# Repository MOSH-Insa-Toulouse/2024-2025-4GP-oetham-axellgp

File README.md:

# 2024-2025-4GP-oetham-axellgp

## Contexte

Projet réalisé dans le cadre du cours "du capteur au banc de test", lors du deuxième semestre de l'année 2024-2025 de la formation 4ème année Génie Physique. Notre point de référence est l'article _"Pencil Drawn Strain Gauges and Chemiresistors on Paper"_ (Cheng-Wei Lin, Zhibo Zhao, Jaemyung Kim & Jiaxing Huang). Notre capteur est composé d'un simple bout de papier avec du graphite déposé dessus par un crayon à papier. Avec une simple déformation du papier, nous pouvons mesurer la déformation des particules. Le système granulaire du papier subit une modification de résistance et de conductance. Ainsi, nous pourrons utiliser ce capteur comme une jauge de contrainte traditionnelle.

L'objectif de ce projet est de pouvoir réaliser, étape par étape, un dispositif qui nous permettra de mesurer une déformation d'un capteur low-tech.

## Sommaire

- [Contexte](#contexte)
- [Sommaire](#sommaire)
- [Livrables](#livrables)
- [Matériel nécessaire](#matériel-nécessaire)
- [Simulation sur LTSpice](#simulation-sur-ltspice)
- [Design du PCB](#design-du-pcb)
- [Réalisation du Shield](#réalisation-du-shield)
- [Code Arduino](#code-arduino)
- [Application MIT](#application-mit)
- [Datasheet](#datasheet)
- [Conclusion](#conclusion)
- [Contact](#contact)

## Livrables

- Un shield PCB permettant à se relier à une carte Arduino UNO. Ce shield aura à disposition plusieurs composants : un capteur de graphite, un module bluetooth, un ecran OLED, un encodeur rotatoire et un amplificateur transimpédance avec un potentiometre digital.
- Un code Arduino qui pilotera les différents composants.
- Une application Android réalisée sous MIT App Inventor.
- Une datasheet du capteur de graphite avec les données venant d'un banc de test mis en place par les étudiants.

## Matériel nécessaire

Pour produire notre shield, nous avons besoin du matériel suivant :

- Des résistances
- Des capacités
- Un Arduino UNO
- Un amplificateur opérationnel (LTC1050)
- Un potentiomètre digital (MCP41050)
- Un écran OLED
- Un encodeur rotatoire
- Un module bluetooth (HC-05)
- Un servo moteur
- Un flex sensor

## Simulation sur LTSpice

La résistance interne de notre capteur de graphite est de l'ordre du $\text{G}\Omega$. Le courant généré lorsque nous appliquons une tension de 5V est très faible. Pour pouvoir utiliser ce signal, nous le faisons passer par un amplificateur transimpédance. Ce montage est constitué d'un amplificateur opérationnel (AO) pour fournir un signal suffisamment large au convertisseur analogique-numérique (ADC) de l'Arduino UNO.

Nous avons choisi un AO de type LTC1050, car il possède une capacité à accepter en entrée un courant très faible et un offset de tension bas. Nous avons besoin d'un offset faible pour ne pas fausser les valeurs de tension envoyées à l'ADC que nous aurons besoin pour la suite.

Dans notre amplificateur, nous avons trois types de filtres différents :

- À l'entrée, un filtre passe-bas passif (composants : $R_1, C_1$) avec une fréquence de coupure de 16Hz. Cela permet de filtrer les bruits du courant en entrée.
- Un autre filtre passe-bas actif de fréquence de coupure de 1.6Hz (composants : $R_3, C_4$) couplé à l'AO. Ce filtre permet d'enlever la composante du bruit à 50Hz du réseau.
- En sortie, un dernier filtre (composants : $R_6, C_2$) de 1.6kHz qui permet de retirer le bruit créé pendant le traitement i.e. bruits des alimentations, de l'horloge...

La résistance $R_5$ est placé en amont de l'AO pour le protéger contre des décharges électrostatiques. Pour notre simulation, nous avons placé la capacité $C_3$ de sorte à ce qu'elle filtre le bruit de l'alimentation. Ainsi, la résistance $R_2$ sera remplacé par une résistance variable (un potentiomètre digital) qui va nous permettre de régler le gain de notre AO en fonction de notre besoin.

Une photo pour montrer que notre montage permet à amplifier notre signal du capteur :

Le signal de sortie est amplifié à 1V, ce qui sera assez pour que notre Arduino puisse le mesurer.

Ensuite, la réponse lorsque nous simulons un courant alternatif pour vérifier que le bruit est bien filtré :

Le bruit du réseau est atténué d'environ 72dB.

La simulation se trouve dans [ce dossier](/LTSpice/).

## Design du PCB

Pour réaliser notre printed circuit board (PCB), nous avons utilisé le logiciel KiCAD 9.0. Dans le logiciel, nous disposons de plusieurs outils de design comme la vue schématique des composants et la vue design du PCB.

La résistance $\text{R}_2$ a été remplace par un potentiomètre numérique de manière à faire varier le gain de notre amplificateur opérationnel (LTC1050). Nous avons également rajouté des composants en plus pour mesurer plus précisément notre capteur graphite. Ces composants seront déposés sur un shield d'Arduino UNO construit à partir d'un Gerber KiCAD.

- Un flex sensor
- Un écran OLED
- Un servo moteur
- Un module bluetooth HC-05

Ensuite, nous avons commencé par réaliser les symboles des composants avec leur schéma électrique sur la partie schématique de KiCAD. Le schéma électrique de l'ensemble de notre shield :

Par la suite, nous avons créé les empreintes de nos composants puis placées sur notre PCB sur la face PCB de KiCAD. Notre objectif pendant le routage était d'éviter les vias entraînées par le placement des composants. Le PCB créé sur le logiciel :

La beauté du logiciel est due au fait que nous pouvons générer une vue 3D du shield afin de pouvoir visualiser et vérifier l'emplacement de nos composants. La vue 3D sur KiCAD :

Vous pouvez retrouver toutes les ressources de KiCAD dans notre [dossier KiCAD](/KiCAD/projet-capteur/).

## Réalisation du Shield

Avec l'aide de Catherine Crouzet (aka Cathy pour les 4GP), nous avons fabriqué notre propre PCB. Après avoir envoyé notre fichier Gerber, qui sert comme masque de gravure, Cathy a placé ce masque sur une couche fine de cuivre sur une plaquette d'epoxy. Ensuite, il faut isoler la plaquette, puis l'expose aux UV. Une fois terminer, elle plonge la plaquette dans un bain révélateur afin de retirer la résine non-isolée. Finalement, elle nettoie la plaquette avec de l'acétone pour enlever la résine restante.

Nous avons ensuite effectué au perçage de notre plaquette grâce à une perceuse. On pourra ensuite poser et souder nos composants sur le PCB.

Voici une photo du PCB sur l'Arduino UNO avec tout les composants poser dessus :

## Code Arduino

Le code Arduino a été développé sur l'IDE Arduino 2.3.5. Nous avons utilisé les librairies Adafruit_SSD1306 pour piloter l'écran OLED et SoftwareSerial pour le HC-05. L'écran OLED utilise beaucoup de RAM. Pour contourner ce problème, nous avons utilisé la fonction ```F("Enter String")``` qui envoie les données sur la mémoire flash.

Au lancement du programme, qui est situé [ici](/Arduino/Test-Sensor/), une première calibration est faite à 3V sur le potentiomètre digital pour ne pas saturer la sortie sur l'ADC de l'Arduino. Cette calibration peut être refaite avec un simple appel sur l'application. Nous avons composé un menu avec trois choix :

- Menu 1 : Graphite Sensor
- Menu 2 : Flex Sensor
- Menu 3 : Servo Motor

Le choix du menu se fait avec l'encodeur rotatoire en le tournant pour sélectionner son menu désiré puis ensuite appuyer dessus pour valider la sélection.

Chaque choix du menu appelle une fonction différente qui réalise sa mesure. L'acquisition des données se fait toutes les 200ms. Pour chaque donnée, il faut convertir ce qu'on reçoit par la résolution de l'Arduino qui est de 1024 bytes. Le calcul de la résistance du capteur graphite se fait avec la formule suivante : $R_{es} = R_2 * (1 + \frac{R_4}{R_3}) * \frac{V_{CC}}{V_{graph}} - R_2 - R_1$. L'appellation des résistances est en accord avec notre schématique KiCAD.

## Application MIT

L'application Android a été développé sous MIT App Inventor. Elle reçoit les donnes de notre Capteur Graphite et de Flexion et nous pouvons aussi lui envoyer une position pour le Servo Moteur.

La face-avant de l'application nous donne la possibilité de rentrée dans plusieurs menus :

- Capteur Graphite
- Capteur Flexion
- Servo Moteur

Une fonctionnalité du menu Capteur Graphite est que nous pouvions calibrer directement le capteur depuis l'application s'il y a eu des changements de configuration.

Le menu Capteur Flexion propose un graphique où nous voyons la variation de la résistance du capteur.

Le menu Servo Moteur propose une roue tactile que nous pouvons régler afin d'envoyer la position désirer du Servo Moteur.

Vous pouvez vous rendre dans [ce dossier](/Android/) pour installer l'application MIT App Inventor ainsi voir les blocks de code qui contrôlent l'application.

## Datasheet

Pour effectuer des mesures, nous avons utilisé une impression 3D de demi-cercles avec des rayons différents.

Les diamètres des demi-cercles vont de 2cm jusqu'à 5cm avec un pas de 0.5cm. Avec la déformation $\epsilon = \frac{e}{D}$ et la résistance électrique $\frac{\Delta R}{R_0}$, nous pouvons tracer les courbes caractéristiques pour des crayons de type F, HB, 4B, 5B :

D'autant plus, nous n'avons aucun moyen pour bien s'assurer que la quantité déposée sur le capteur est la même. Ainsi, à chaque mesure, il y a un nouveau paramètre qui n'est pas le même i.e. on n'écrit pas de la même manière, on applique une force différente pour écrire, on n'applique pas le même angle de déformation. Ces derniers induisent une grosse variation dans la résistance mesurée.

Il se trouve que le flex sensor commercial est bien plus sensible à la déformation d'autant plus il peut être réutiliser beaucoup plus de fois que notre capteur en papier. Notre capteur a chaque utilisation perd de la précision qui impacte notre mesure de résistance. Par contre, notre capteur peut mesurer des résistances dans les $M\Omega$ comparer au flex sensor qui lui peut seulement mesurer des $k\Omega$.

La datasheet se trouve [ici](/Datasheet/).

## Conclusion

Notre capteur a un super potentiel en tant que capteur industriel. Il faudrait à tout prix trouver une méthode pour homogénéiser le dépôt du graphite. Le capteur est peu cher et sensible à des variations en tension ou compression. Nous conseillons de trouver une méthode pour bien appliquer la même force, le même dépôt de graphite et aussi trouver un papier plus adapté à la déformation. Ceci permettra de réaliser un capteur plus performant avec un potentiel plus élevé pour être industrialisable.

Pour le moment, notre capteur en papier est un super outil pour pouvoir comprendre et conceptionner notre propre PCB et ainsi un banc de test afin de mesurer des quantités physiques qui peuvent nous intéresser. Effectivement, le capteur présente beaucoup de lacunes de précisions et le matériel à disposition ne fonctionne pas parfaitement. Ce capteur est l'outil pédagogique ultime et nous permet d'apprendre et de peaufiner des nouvelles connaissances.

## Contact

Pour toutes questions, vous pouvez nous contacter aux adresses suivantes :

- Mathéo HAHN : <hahn@insa-toulouse.fr>
- Axel LONGEPIERRE : <longepierre@insa-toulouse.fr>

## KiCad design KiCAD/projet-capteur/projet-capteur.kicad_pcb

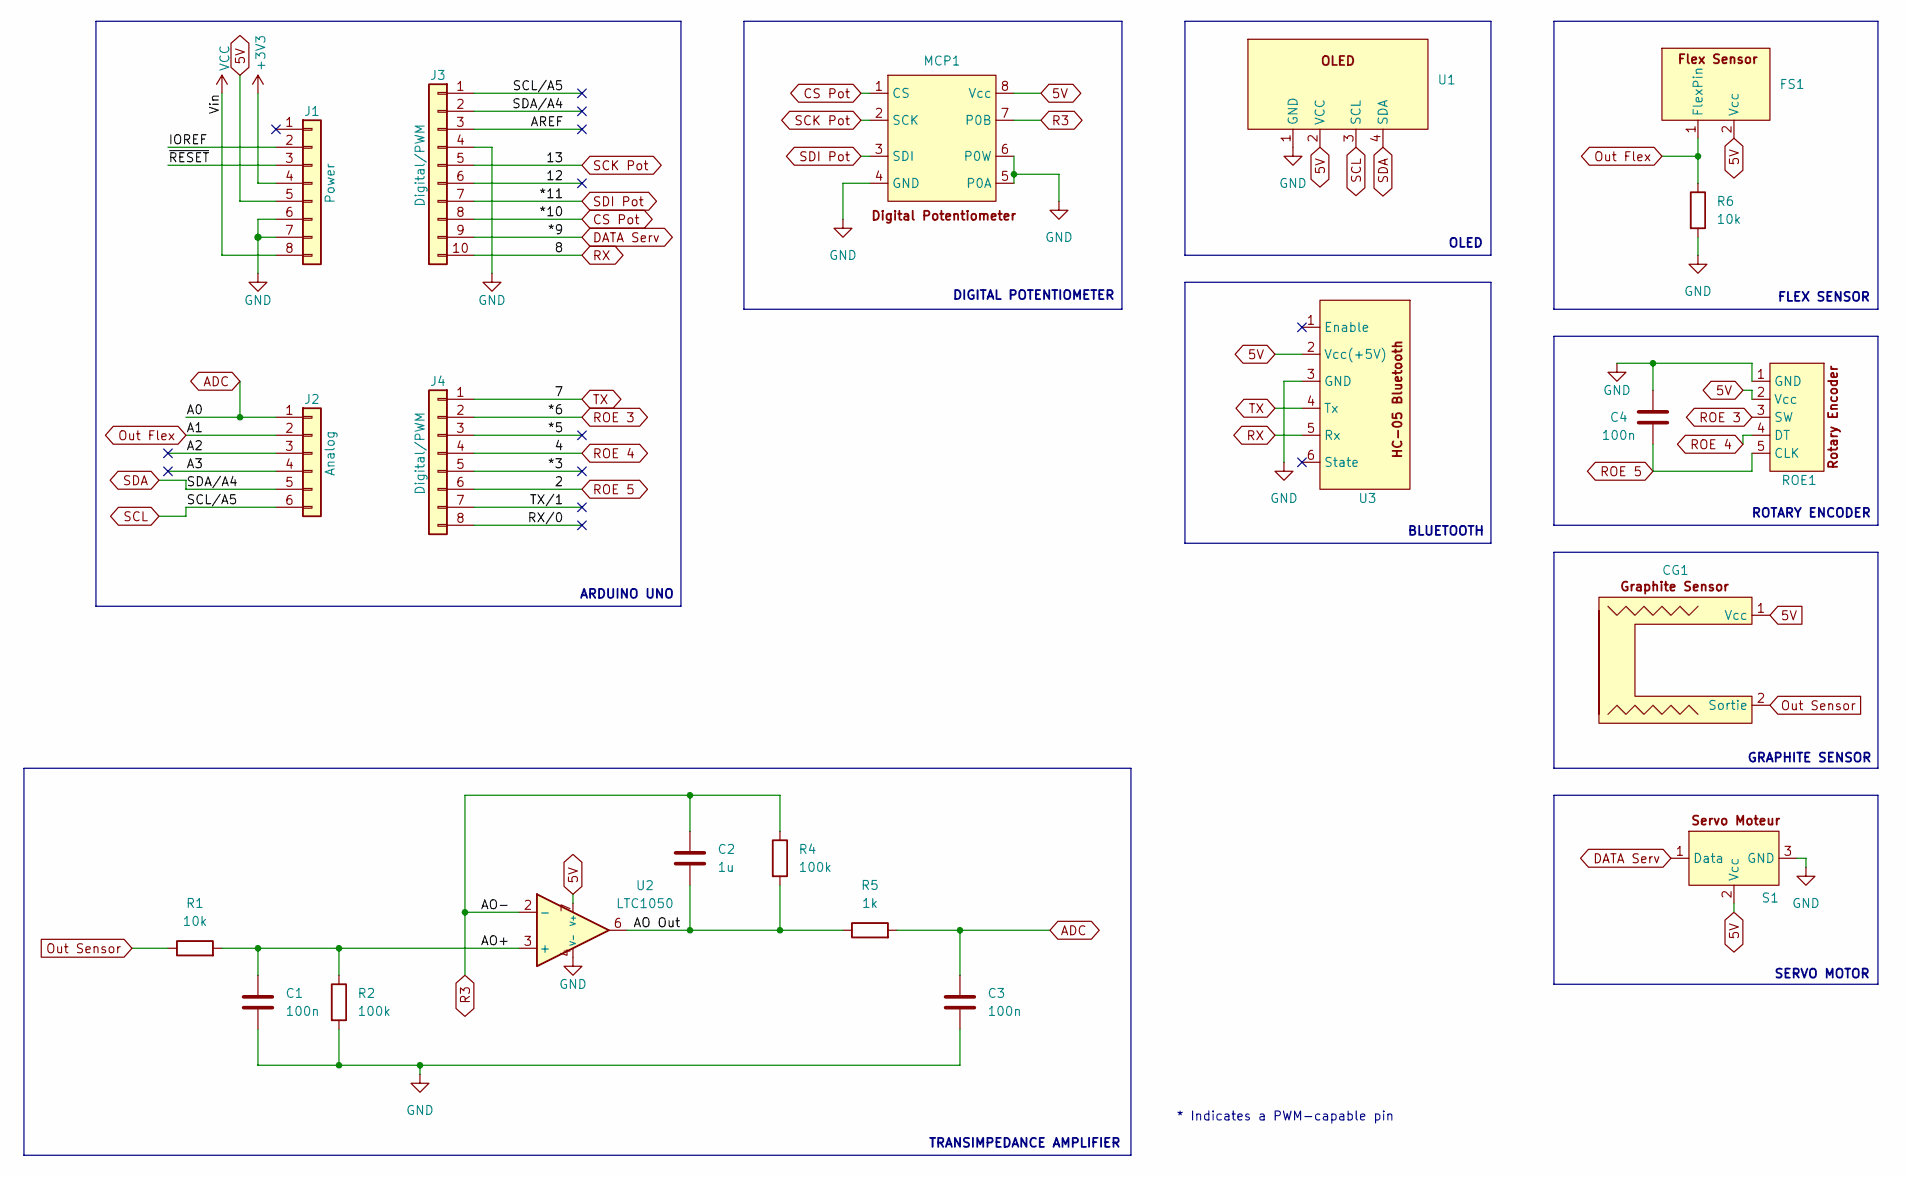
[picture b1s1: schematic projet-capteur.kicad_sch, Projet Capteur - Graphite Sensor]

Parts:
C1, C3, C4: 100n; C_Disc_D6.0mm_W2.5mm_P5.00mm
C2: 1u; C_Disc_D6.0mm_W2.5mm_P5.00mm
CG1: Capteur Graphene
FS1: Flex Sensor
J1: Power; PinSocket_1x08_P2.54mm_Vertical
J2: Analog; PinSocket_1x06_P2.54mm_Vertical
J3: Digital/PWM; PinSocket_1x10_P2.54mm_Vertical
J4: Digital/PWM; PinSocket_1x08_P2.54mm_Vertical
MCP1: DIP-8_W7.62mm
R1, R6: 10k; R_Axial_DIN0207_L6.3mm_D2.5mm_P5.08mm_Vertical
R2, R4: 100k; R_Axial_DIN0207_L6.3mm_D2.5mm_P5.08mm_Vertical
R5: 1k; R_Axial_DIN0207_L6.3mm_D2.5mm_P5.08mm_Vertical
ROE1: RotaryEncoder
S1: ServoMoteur
U1: MyEmpreinte
U2: LTC1050; DIP-8_W7.62mm
U3: HC-05

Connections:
5V: CG1.1 (Vcc), FS1.2 (Vcc), J1.5, MCP1.8 (Vcc), ROE1.2 (Vcc), S1.2 (Vcc), U1.2 (VCC), U2.7 (V+), U3.2 (Vcc(+5V))
+3V3: J1.4
/12: J3.6
/*3: J4.5
/*5: J4.3
/A2: J2.3
/A3: J2.4
/AO Out: C2.2, R4.2, R5.1, U2.6
/AO+: C1.1, R1.2, R2.1, U2.3 (+)
/AREF: J3.3
/IOREF: J1.2
/RX/0: J4.8
/TX/1: J4.7
/~RESET: J1.3
ADC: C3.1, J2.1, R5.2
CS Pot: J3.8, MCP1.1 (CS)
DATA Serv: J3.9, S1.1 (Data)
GND: C1.2, C3.2, C4.1, J1.6, J1.7, J3.4, MCP1.4 (GND), MCP1.5 (P0A), MCP1.6 (P0W), R2.2, R6.2, ROE1.1 (GND), S1.3 (GND), U1.1 (GND), U2.4 (V-), U3.3 (GND)
Out Flex: FS1.1 (FlexPin), J2.2, R6.1
Out Sensor: CG1.2 (Sortie), R1.1
R3: C2.1, MCP1.7 (P0B), R4.1, U2.2 (-)
ROE 3: J4.2, ROE1.3 (SW)
ROE 4: J4.4, ROE1.4 (DT)
ROE 5: C4.2, J4.6, ROE1.5 (CLK)
RX: J3.10, U3.5 (Rx)
SCK Pot: J3.5, MCP1.2 (SCK)
SCL: J2.6, J3.1, U1.3 (SCL)
SDA: J2.5, J3.2, U1.4 (SDA)
SDI Pot: J3.7, MCP1.3 (SDI)
TX: J4.1, U3.4 (Tx)
VCC: J1.8

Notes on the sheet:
ROTARY ENCODER
GRAPHITE SENSOR
DIGITAL POTENTIOMETER
ARDUINO UNO
FLEX SENSOR
SERVO MOTOR
BLUETOOTH
* Indicates a PWM-capable pin
OLED
TRANSIMPEDANCE AMPLIFIER

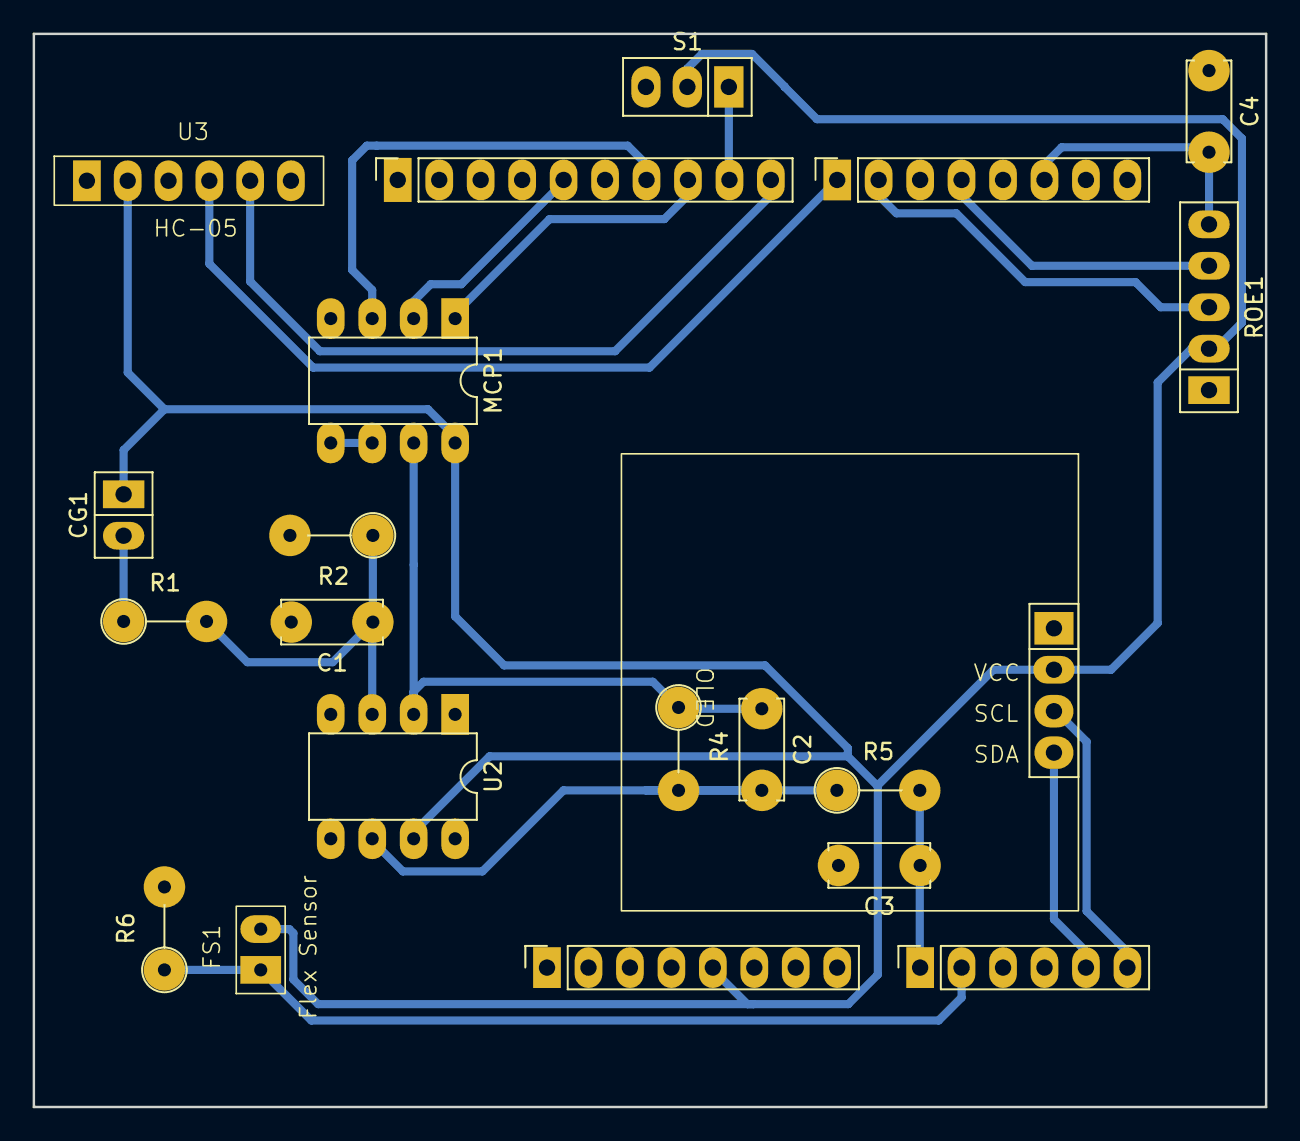
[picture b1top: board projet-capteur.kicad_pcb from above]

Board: 2 copper layers, 75.5 x 65.8 mm, 21 parts (0 on the bottom side), 19 nets.

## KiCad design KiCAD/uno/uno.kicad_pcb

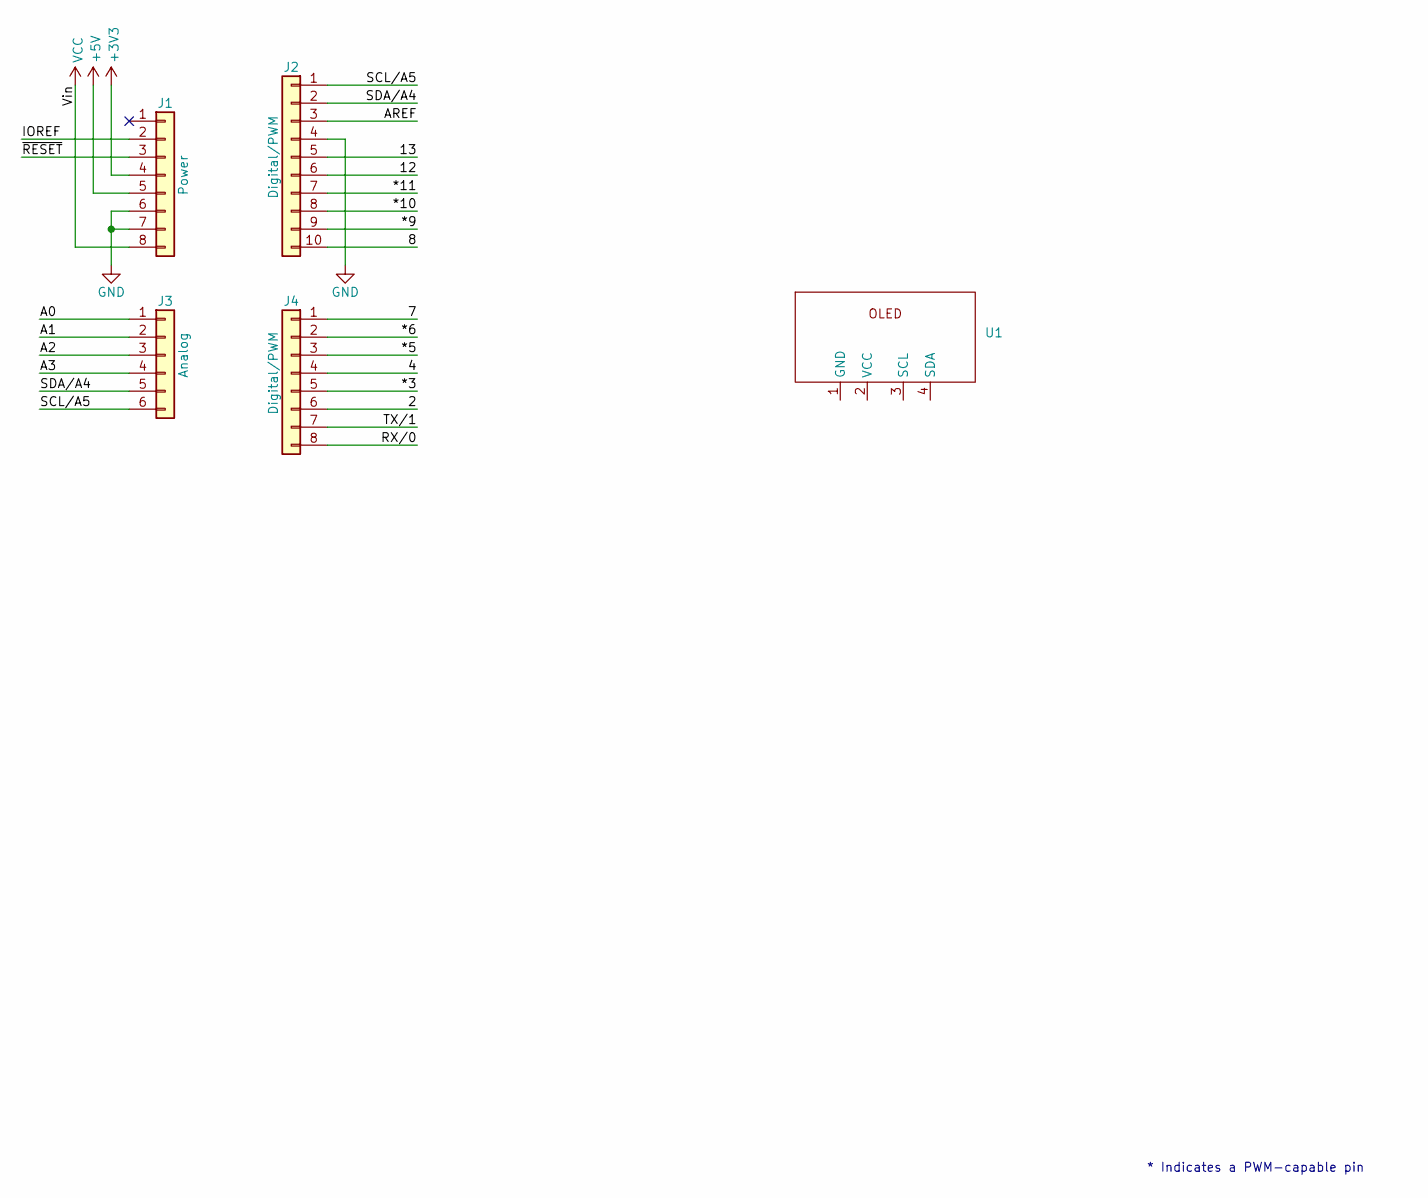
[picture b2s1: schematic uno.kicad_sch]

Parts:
J1: Power; PinSocket_1x08_P2.54mm_Vertical
J2: Digital/PWM; PinSocket_1x10_P2.54mm_Vertical
J3: Analog; PinSocket_1x06_P2.54mm_Vertical
J4: Digital/PWM; PinSocket_1x08_P2.54mm_Vertical
U1: MyEmpreinte

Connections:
+3V3: J1.4
+5V: J1.5
/2: J4.6
/4: J4.4
/7: J4.1
/8: J2.10
/12: J2.6
/13: J2.5
/*3: J4.5
/*5: J4.3
/*6: J4.2
/*9: J2.9
/*10: J2.8
/*11: J2.7
/A0: J3.1
/A1: J3.2
/A2: J3.3
/A3: J3.4
/AREF: J2.3
/IOREF: J1.2
/RX/0: J4.8
/SCL/A5: J2.1, J3.6
/SDA/A4: J2.2, J3.5
/TX/1: J4.7
/~RESET: J1.3
GND: J1.6, J1.7, J2.4
VCC: J1.8

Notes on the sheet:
* Indicates a PWM-capable pin

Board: 2 copper layers, 9 parts (0 on the bottom side), 3 nets, no tracks yet.

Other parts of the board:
MH1, MH2, MH3, MH4: MountingHole_3.2mm

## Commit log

2025-02-19 Ajout du fichier Bonjour
2025-03-05 Ajout des fichiers de bases
2025-03-08 Remis les empreintes perdues
2025-03-08 Ajout ecran OLED + Schema
2025-03-08 Ajout du HC-05
2025-03-08 rajout des condesateur sur le pcb
2025-03-08 pin a jour pour le ltc1050 hc05 connecté
2025-03-10 Ajout du Flex Sensor et DPotentiometre
2025-03-12 Ajout du header Servo Moteur
2025-03-12 Seance Realisation du shield 12.03
2025-03-12 Seance Realisation du shield 12.03 v2
2025-03-12 Ajout dossier Gerber
2025-03-12 Changement des positions du encodeur
2025-03-13 Seance Realisation du shield 13.03
2025-03-16 Modif des tracks + pins
2025-03-16 Reparation des pins du potentiometre
2025-03-17 Correction du Bluetooth
2025-03-17 Seance Realisation banc de test 17.03
2025-03-17 Grandissement du shield
2025-03-18 Modif Rot
2025-03-18 Beautification du PCB
2025-03-28 Datasheet
2025-03-28 Datasheet - Termine premiere page
2025-03-28 Ajout du dossier Arduino
2025-03-31 Amelioration de la Datasheet
2025-03-31 Fonctionalite du menu
2025-03-31 Datasheet - Electric Diagram
2025-04-01 Datasheet - Applications
2025-04-02 Menu Flex
2025-04-03 Trop coooooll
2025-04-05 Modif du README
2025-04-07 Arduino - Menu presque fini
2025-04-07 README - Modif et Arduino - Menu 3
2025-04-08 Arduino - Modif du 08.04
2025-04-08 Beautification du Schematique
2025-04-10 README - LTSpice et Realisation Shield
2025-04-10 README - Ajout des photos simu
2025-04-11 Test Bench
2025-04-13 Ajout dossier LTSpice
2025-04-14 Datasheet - Correction typos et Arduino - Fonction Calibration
2025-04-15 Arduino - Click Switch
2025-04-17 Arduino - Comments added
2025-04-24 Arduino - Fonction recevoir BT
2025-04-26 Reception bleutooth mise en place + controle app to arduino
2025-04-26 appli android rajouter
2025-04-27 Arduino - Comments + Correction et ReadME - Android et Arduino
2025-04-29 Update Test-Sensor.ino version final coté axel
2025-04-29 Arduino - Improved readability
2025-05-21 Update Final Test-Sensor.ino
    FINITOT pipo
2025-05-24 Final Version
